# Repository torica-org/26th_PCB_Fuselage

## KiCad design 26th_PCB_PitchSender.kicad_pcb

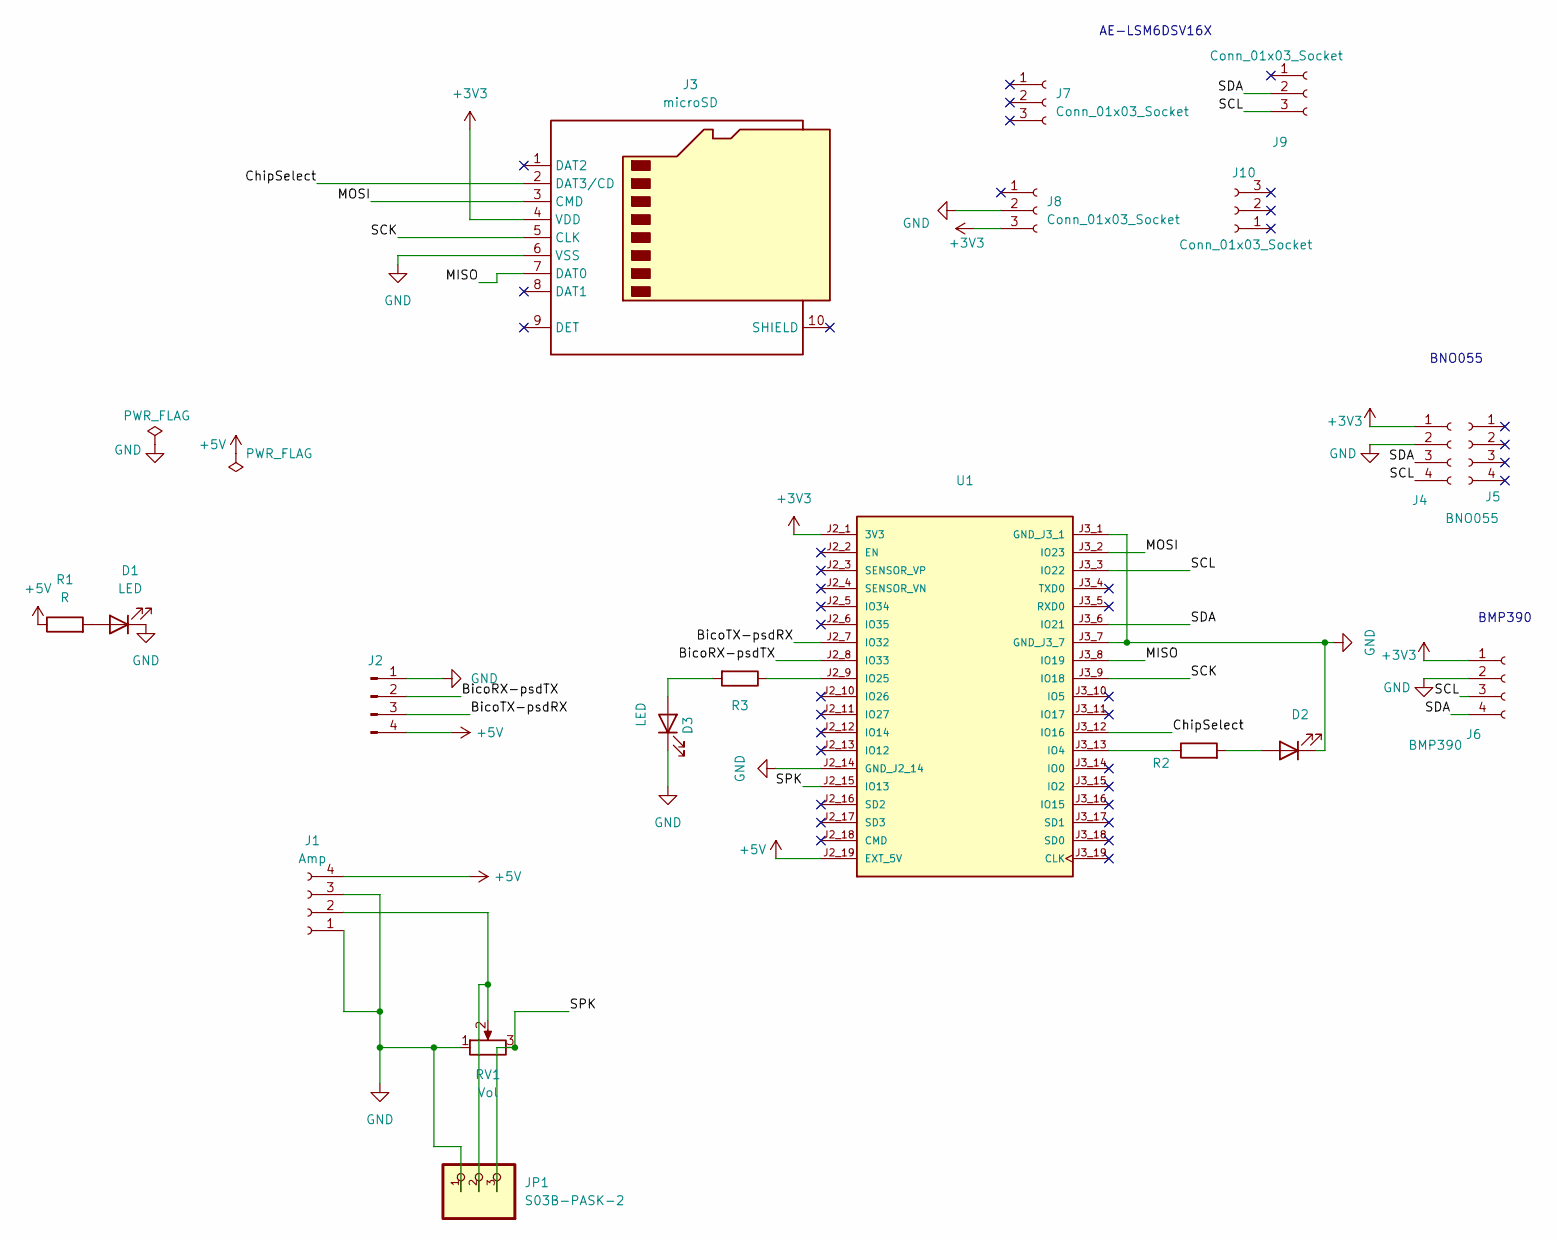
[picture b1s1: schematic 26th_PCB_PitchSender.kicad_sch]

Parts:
D1, D2, D3: LED; LED_D3.0mm
J1: Amp; PinHeader_1x04_P2.54mm_Vertical
J2: Conn_01x04_Pin; JST_S04B-PASK-2_LF__SN_
J3: microSD; PinHeader_1x10_P2.54mm_Vertical
J4: Conn_01x04_Socket; PinHeader_1x04_P2.54mm_Vertical
J5: BNO055; PinHeader_1x04_P2.54mm_Vertical
J6: BMP390; PinHeader_1x04_P2.54mm_Vertical
J7, J8, J9, J10: Conn_01x03_Socket; PinSocket_1x03_P2.54mm_Vertical
JP1: S03B-PASK-2
R1, R2, R3: R; R_Axial_DIN0204_L3.6mm_D1.6mm_P5.08mm_Horizontal
RV1: Vol; PinHeader_1x03_P2.54mm_Vertical
U1: MODULE_ESP32-DEVKITC-32E; PARTREV 1.4

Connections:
+3V3: J3.4 (VDD), J4.1, J6.1, J8.3, U1.J2_1 (3V3)
+5V: J1.4, J2.4, R1.1, U1.J2_19 (EXT_5V)
/BicoRX-psdTX: J2.2, U1.J2_8 (IO33)
/BicoTX-psdRX: J2.3, U1.J2_7 (IO32)
/ChipSelect: J3.2 (DAT3/CD), U1.J3_12 (IO16)
/MISO: J3.7 (DAT0), U1.J3_8 (IO19)
/MOSI: J3.3 (CMD), U1.J3_2 (IO23)
/SCK: J3.5 (CLK), U1.J3_9 (IO18)
/SCL: J4.4, J6.3, J9.3, U1.J3_3 (IO22)
/SDA: J4.3, J6.4, J9.2, U1.J3_6 (IO21)
/SPK: JP1.3, RV1.3, U1.J2_15 (IO13)
GND: D1.1 (K), D2.1 (K), D3.1 (K), J1.1, J1.3, J2.1, J3.6 (VSS), J4.2, J6.2, J8.2, JP1.1, RV1.1, U1.J2_14 (GND_J2_14), U1.J3_1 (GND_J3_1), U1.J3_7 (GND_J3_7)
unnamed: D1.2 (A), R1.2
unnamed: D2.2 (A), R2.2
unnamed: D3.2 (A), R3.2
unnamed: J1.2, JP1.2, RV1.2
unnamed: R2.1, U1.J3_13 (IO4)
unnamed: R3.1, U1.J2_9 (IO25)

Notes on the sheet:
BNO055
BMP390
AE-LSM6DSV16X

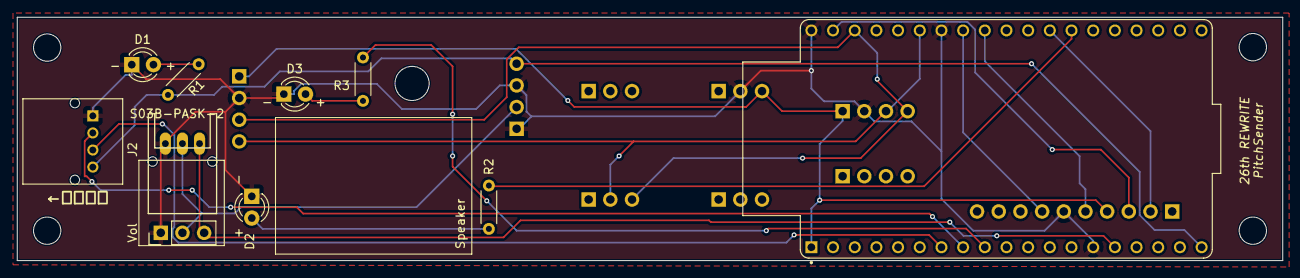
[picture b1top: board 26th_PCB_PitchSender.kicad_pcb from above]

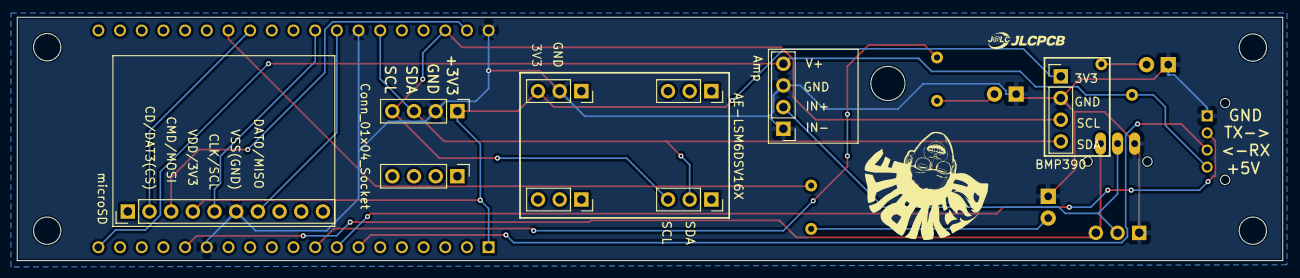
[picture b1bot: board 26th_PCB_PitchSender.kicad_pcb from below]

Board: 2 copper layers, 148.2 x 28.5 mm, 26 parts (11 on the bottom side), 18 nets.

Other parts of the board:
H1, H2, H3, H4, H5: MountingHole_3.2mm_M3
JLCPCB_LOGO: LOGO; JLCPCB(9mm)
REWRITE_LOGO: LOGO; REWRITE_LOGO

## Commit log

2026-05-26 PCB配線途中
2026-05-26 Add status LED
2026-05-27 ESP32とスピーカー場所交代
2026-05-28 コネクタ向き修正
2026-05-29 UART/LEDピン変更
2026-05-31 配線用穴そばの配線ほんのちょっと変更
2026-05-31 配線ちょっと変更
2026-05-31 Add IMU
